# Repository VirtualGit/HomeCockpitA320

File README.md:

# A320 Home Cockpit
Home cockpit project of the Airbus A320 based on Arduino.

[Read more](https://github.com/VirtualGit/HomeCockpitA320/wiki/A320-Home-Cockpit)

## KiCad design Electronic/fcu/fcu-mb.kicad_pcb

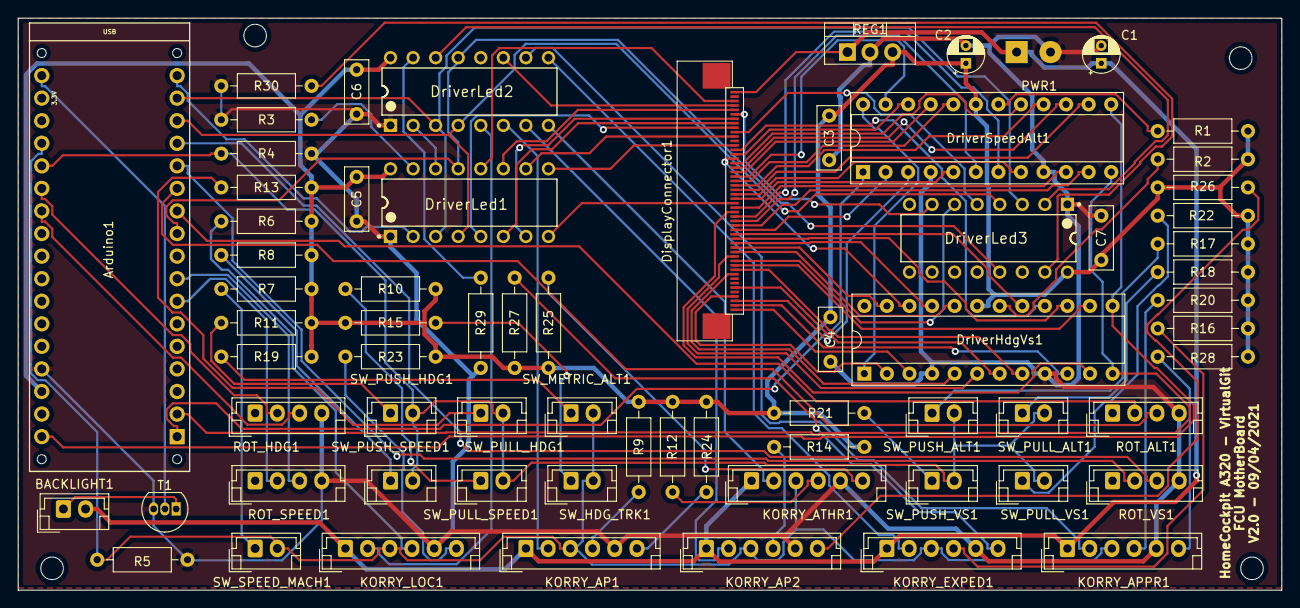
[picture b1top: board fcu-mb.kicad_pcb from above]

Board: 2 copper layers, 142.2 x 64.4 mm, 69 parts (0 on the bottom side), 103 nets.

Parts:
Arduino1: Arduino_Nano_v3.x; Arduino_Micro_Socket
BACKLIGHT1: Conn_01x02_Male; JST_EH_B2B-EH-A_1x02_P2.50mm_Vertical
C1: 100µF; CP_Radial_D4.0mm_P2.00mm
C2: 10µF; CP_Radial_D4.0mm_P2.00mm
C3, C4: 0,1µF; C_Disc_D7.0mm_W2.5mm_P5.00mm
C5, C6, C7: 1µF; C_Disc_D7.0mm_W2.5mm_P5.00mm
DisplayConnector1: Connector-FPC-50pins; Connector-FPC-50pins-0.5mm
DriverHdgVs1: MAX7219; DIP-24_W7.62mm_Socket
DriverLed1, DriverLed2, DriverLed3: TLC5917IN; Texas_Instruments-TLC5917IN-Manufacturer_Recommended
DriverSpeedAlt1: MAX7219; DIP-24_W7.62mm_Socket
KORRY_AP1, KORRY_AP2: Korry; JST_EH_B6B-EH-A_1x06_P2.50mm_Vertical
KORRY_APPR1: Korry; JST_EH_B6B-EH-A_1x06_P2.50mm_Vertical
KORRY_ATHR1: Korry; JST_EH_B6B-EH-A_1x06_P2.50mm_Vertical
KORRY_EXPED1: Korry; JST_EH_B6B-EH-A_1x06_P2.50mm_Vertical
KORRY_LOC1: Korry; JST_EH_B6B-EH-A_1x06_P2.50mm_Vertical
PWR1: Conn_Coaxial_Power; SolderWirePad_1x02_P3.81mm_Drill1mm
R1, R2: 9,53kohms; R_Axial_DIN0207_L6.3mm_D2.5mm_P10.16mm_Horizontal
R3, R29: 1kohms; R_Axial_DIN0207_L6.3mm_D2.5mm_P10.16mm_Horizontal
R4, R5: 100kOhms; R_Axial_DIN0207_L6.3mm_D2.5mm_P10.16mm_Horizontal
R6, R13: 33kOhms; R_Axial_DIN0207_L6.3mm_D2.5mm_P10.16mm_Horizontal
R7, R8: 8,2kOhms; R_Axial_DIN0207_L6.3mm_D2.5mm_P10.16mm_Horizontal
R9, R22: 120kOhms; R_Axial_DIN0207_L6.3mm_D2.5mm_P10.16mm_Horizontal
R10, R15: 15kOhms; R_Axial_DIN0207_L6.3mm_D2.5mm_P10.16mm_Horizontal
R11, R19: 22kOhms; R_Axial_DIN0207_L6.3mm_D2.5mm_P10.16mm_Horizontal
R12, R17: 47kOhms; R_Axial_DIN0207_L6.3mm_D2.5mm_P10.16mm_Horizontal
R14: 150kOhms; R_Axial_DIN0207_L6.3mm_D2.5mm_P10.16mm_Horizontal
R16, R18: 68kOhms; R_Axial_DIN0207_L6.3mm_D2.5mm_P10.16mm_Horizontal
R20, R21: 91kOhms; R_Axial_DIN0207_L6.3mm_D2.5mm_P10.16mm_Horizontal
R23, R24, R25, R26, R27, R28: 100Ohms; R_Axial_DIN0207_L6.3mm_D2.5mm_P10.16mm_Horizontal
R30: 2kohms; R_Axial_DIN0207_L6.3mm_D2.5mm_P10.16mm_Horizontal
REG1: L7805; TO-220-3_Vertical
ROT_ALT1: Rotary_Encoder; JST_EH_B4B-EH-A_1x04_P2.50mm_Vertical_RotaryEncoder
ROT_HDG1: Rotary_Encoder; JST_EH_B4B-EH-A_1x04_P2.50mm_Vertical_RotaryEncoder
ROT_SPEED1: Rotary_Encoder; JST_EH_B4B-EH-A_1x04_P2.50mm_Vertical_RotaryEncoder
ROT_VS1: Rotary_Encoder; JST_EH_B4B-EH-A_1x04_P2.50mm_Vertical_RotaryEncoder
SW_HDG_TRK1: SW_Push; JST_EH_B2B-EH-A_1x02_P2.50mm_Vertical
SW_METRIC_ALT1: SW_Push; JST_EH_B2B-EH-A_1x02_P2.50mm_Vertical
SW_PULL_ALT1: SW_Push; JST_EH_B2B-EH-A_1x02_P2.50mm_Vertical
SW_PULL_HDG1: SW_Push; JST_EH_B2B-EH-A_1x02_P2.50mm_Vertical
SW_PULL_SPEED1: SW_Push; JST_EH_B2B-EH-A_1x02_P2.50mm_Vertical
SW_PULL_VS1: SW_Push; JST_EH_B2B-EH-A_1x02_P2.50mm_Vertical
SW_PUSH_ALT1: SW_Push; JST_EH_B2B-EH-A_1x02_P2.50mm_Vertical
SW_PUSH_HDG1: SW_Push; JST_EH_B2B-EH-A_1x02_P2.50mm_Vertical
SW_PUSH_SPEED1: SW_Push; JST_EH_B2B-EH-A_1x02_P2.50mm_Vertical
SW_PUSH_VS1: SW_Push; JST_EH_B2B-EH-A_1x02_P2.50mm_Vertical
SW_SPEED_MACH1: SW_Push; JST_EH_B2B-EH-A_1x02_P2.50mm_Vertical
T1: BS170; TO-92_Inline

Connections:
+5V: Arduino1.VIN, C2.1, C3.1, C4.1, C5.2, C6.2, C7.2, DriverHdgVs1.19, DriverLed1.16, DriverLed2.16, DriverLed3.16, DriverSpeedAlt1.19, R1.1, R2.1, R6.2, R7.2, R8.2, R9.2, R10.2, R11.2, R12.2, R13.2, R14.2, R15.2, R16.2, R17.2, R18.2, R19.2, R20.2, R21.2, R22.2, R23.2, R24.2, R25.2, R26.2, R27.2, R28.2, REG1.3
BTN_GRP_1: Arduino1.A0, KORRY_AP1.3, KORRY_AP2.3, KORRY_APPR1.3, KORRY_ATHR1.3, KORRY_EXPED1.3, KORRY_LOC1.3, R5.2, SW_HDG_TRK1.2, SW_METRIC_ALT1.2, SW_SPEED_MACH1.2
BTN_GRP_2: Arduino1.A1, R4.2, SW_PULL_ALT1.2, SW_PULL_HDG1.2, SW_PULL_SPEED1.2, SW_PULL_VS1.2, SW_PUSH_ALT1.2, SW_PUSH_HDG1.2, SW_PUSH_SPEED1.2, SW_PUSH_VS1.2
DriverDigitClock: Arduino1.SCK, DriverHdgVs1.13, DriverSpeedAlt1.13
DriverDigitData: Arduino1.MOSI, DriverSpeedAlt1.1
DriverDigitLoad: Arduino1.SS, DriverHdgVs1.12, DriverSpeedAlt1.12
DriverLedClock: Arduino1.D11, DriverLed1.3, DriverLed2.3, DriverLed3.3
DriverLedData: Arduino1.D12, DriverLed1.2
DriverLedLoad: Arduino1.D10, DriverLed1.4, DriverLed2.4, DriverLed3.4
GND: Arduino1.GND1, C1.2, C2.2, C3.2, C4.2, C5.1, C6.1, C7.1, DriverHdgVs1.4, DriverHdgVs1.9, DriverLed1.1, DriverLed2.1, DriverLed3.1, DriverSpeedAlt1.4, DriverSpeedAlt1.9, KORRY_AP1.5, KORRY_AP2.5, KORRY_APPR1.5, KORRY_ATHR1.5, KORRY_EXPED1.5, KORRY_LOC1.5, PWR1.2, R3.1, R4.1, R5.1, R29.1, R30.1, REG1.2, ROT_ALT1.C, ROT_HDG1.C, ROT_SPEED1.C, ROT_VS1.C, T1.3
LedKorryAP1: DriverLed2.6, KORRY_AP1.2
LedKorryAP2: DriverLed2.7, KORRY_AP2.2
LedKorryAPPR: DriverLed2.10, KORRY_APPR1.2
LedKorryATHR: DriverLed2.8, KORRY_ATHR1.2
LedKorryEXPED: DriverLed2.9, KORRY_EXPED1.2
LedKorryLoc: DriverLed2.5, KORRY_LOC1.2
LedManagedALT: DisplayConnector1.6, DriverLed3.7
LedManagedHDG: DisplayConnector1.39, DriverLed3.6
LedManagedSpeed: DisplayConnector1.10, DriverLed3.5
LedOutputEnable: Arduino1.D5, DriverLed1.13, DriverLed2.13, DriverLed3.13
LedPadFPA: DisplayConnector1.5, DriverLed1.11
LedPadHDG: DisplayConnector1.7, DriverLed1.7
LedPadLAT: DisplayConnector1.13, DriverLed1.9
LedPadMACH: DisplayConnector1.8, DriverLed1.6
LedPadSPD: DisplayConnector1.9, DriverLed1.5
LedPadStaticALT: DisplayConnector1.3, DriverLed1.12
LedPadStaticLines: DisplayConnector1.4, DriverLed2.11
LedPadTRK: DisplayConnector1.26, DriverLed1.8
LedPadVS: DisplayConnector1.11, DriverLed1.10
unnamed: Arduino1.D13, T1.2
unnamed: BACKLIGHT1.1, T1.1
unnamed: DriverHdgVs1.1, DriverSpeedAlt1.24
unnamed: DriverHdgVs1.18, R2.2
unnamed: DriverLed1.14, DriverLed2.2
unnamed: DriverLed1.15, R3.2
unnamed: DriverLed2.14, DriverLed3.2
unnamed: DriverLed2.15, R29.2
unnamed: DriverLed3.15, R30.2
unnamed: DriverSpeedAlt1.18, R1.2
unnamed: KORRY_AP1.4, R9.1
unnamed: KORRY_AP1.6, R24.1
unnamed: KORRY_AP2.4, R14.1
unnamed: KORRY_AP2.6, R26.1
unnamed: KORRY_APPR1.4, R20.1
unnamed: KORRY_APPR1.6, R28.1
unnamed: KORRY_ATHR1.4, R12.1
unnamed: KORRY_ATHR1.6, R25.1
unnamed: KORRY_EXPED1.4, R16.1
unnamed: KORRY_EXPED1.6, R27.1
unnamed: KORRY_LOC1.4, R6.1
unnamed: KORRY_LOC1.6, R23.1
unnamed: R7.1, SW_SPEED_MACH1.1
unnamed: R8.1, SW_PUSH_SPEED1.1
unnamed: R10.1, SW_PULL_SPEED1.1
unnamed: R11.1, SW_PUSH_HDG1.1
unnamed: R13.1, SW_PULL_HDG1.1
unnamed: R15.1, SW_HDG_TRK1.1
unnamed: R17.1, SW_PUSH_ALT1.1
unnamed: R18.1, SW_PULL_ALT1.1
unnamed: R19.1, SW_METRIC_ALT1.1
unnamed: R21.1, SW_PUSH_VS1.1
unnamed: R22.1, SW_PULL_VS1.1
ROT_ALT_A: Arduino1.D6, ROT_ALT1.A
ROT_ALT_B: Arduino1.D7, ROT_ALT1.B
ROT_HDG_A: Arduino1.A2, ROT_HDG1.A
ROT_HDG_B: Arduino1.A3, ROT_HDG1.B
ROT_SPEED_A: Arduino1.D2, ROT_SPEED1.A
ROT_SPEED_B: Arduino1.D3, ROT_SPEED1.B
ROT_VS_A: Arduino1.D8, ROT_VS1.A
ROT_VS_B: Arduino1.D9, ROT_VS1.B
Vcc12V: BACKLIGHT1.2, C1.1, DisplayConnector1.1, KORRY_AP1.1, KORRY_AP2.1, KORRY_APPR1.1, KORRY_ATHR1.1, KORRY_EXPED1.1, KORRY_LOC1.1, PWR1.1, REG1.1
hdgVsA: DisplayConnector1.40, DriverHdgVs1.14
hdgVsB: DisplayConnector1.14, DriverHdgVs1.16
hdgVsC: DisplayConnector1.37, DriverHdgVs1.20
hdgVsD: DisplayConnector1.36, DriverHdgVs1.23
hdgVsDP: DisplayConnector1.16, DriverHdgVs1.22
hdgVsDig0: DisplayConnector1.47, DriverHdgVs1.2
hdgVsDig1: DisplayConnector1.28, DriverHdgVs1.11
hdgVsDig2: DisplayConnector1.38, DriverHdgVs1.6
hdgVsDig3: DisplayConnector1.45, DriverHdgVs1.7
hdgVsDig4: DisplayConnector1.50, DriverHdgVs1.3
hdgVsDig5: DisplayConnector1.49, DriverHdgVs1.10
hdgVsDig6: DisplayConnector1.42, DriverHdgVs1.5
hdgVsDig7: DisplayConnector1.41, DriverHdgVs1.8
hdgVsE: DisplayConnector1.35, DriverHdgVs1.21
hdgVsF: DisplayConnector1.34, DriverHdgVs1.15
hdgVsG: DisplayConnector1.33, DriverHdgVs1.17
speedAltA: DisplayConnector1.23, DriverSpeedAlt1.14
speedAltB: DisplayConnector1.22, DriverSpeedAlt1.16
speedAltC: DisplayConnector1.21, DriverSpeedAlt1.20
speedAltD: DisplayConnector1.20, DriverSpeedAlt1.23
speedAltDP: DisplayConnector1.15, DriverSpeedAlt1.22
speedAltDig0: DisplayConnector1.32, DriverSpeedAlt1.2
speedAltDig1: DisplayConnector1.31, DriverSpeedAlt1.11
speedAltDig2: DisplayConnector1.30, DriverSpeedAlt1.6
speedAltDig3: DisplayConnector1.29, DriverSpeedAlt1.7
speedAltDig4: DisplayConnector1.48, DriverSpeedAlt1.3
speedAltDig5: DisplayConnector1.27, DriverSpeedAlt1.10
speedAltDig6: DisplayConnector1.25, DriverSpeedAlt1.5
speedAltDig7: DisplayConnector1.24, DriverSpeedAlt1.8
speedAltE: DisplayConnector1.19, DriverSpeedAlt1.21
speedAltF: DisplayConnector1.18, DriverSpeedAlt1.15
speedAltG: DisplayConnector1.17, DriverSpeedAlt1.17

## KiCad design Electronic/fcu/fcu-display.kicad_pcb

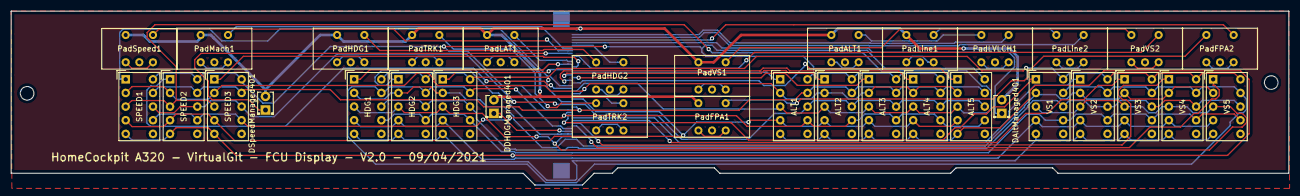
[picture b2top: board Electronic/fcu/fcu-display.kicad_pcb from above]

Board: 2 copper layers, 238.0 x 32.4 mm, 35 parts (1 on the bottom side), 66 nets.

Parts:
ALT1, ALT2, ALT3, ALT4, ALT5: HDSP-7401
DAltManaged401: LED; LED_D2.0mm_W4.0mm_H2.8mm_FlatTop
DDHDGManaged401: LED; LED_D2.0mm_W4.0mm_H2.8mm_FlatTop
DSpeedManaged401: LED; LED_D2.0mm_W4.0mm_H2.8mm_FlatTop
DisplayConnector1: Connector-FPC-50pins; Connector-FPC-50pins-0.5mm
HDG1, HDG2, HDG3: HDSP-7401
PadALT1: LedPad; PadLed-KingBright-DE-2YD
PadFPA1, PadFPA2: LedPad; PadLed-KingBright-DE-2YD
PadHDG1, PadHDG2: LedPad; PadLed-KingBright-DE-2YD
PadLAT1: LedPad; PadLed-KingBright-DE-2YD
PadLVLCH1: LedPad; PadLed-KingBright-DE-2YD
PadLine1, PadLine2: LedPad; PadLed-KingBright-DE-2YD
PadMach1: LedPad; PadLed-KingBright-DE-2YD
PadSpeed1: LedPad; PadLed-KingBright-DE-2YD
PadTRK1, PadTRK2: LedPad; PadLed-KingBright-DE-2YD
PadVS1, PadVS2: LedPad; PadLed-KingBright-DE-2YD
SPEED1, SPEED2, SPEED3: HDSP-7401
VS1, VS2, VS3, VS4, VS5: HDSP-7401

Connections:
LedManagedALT: DAltManaged401.1, DisplayConnector1.45
LedManagedHDG: DDHDGManaged401.1, DisplayConnector1.12
LedManagedSpeed: DSpeedManaged401.1, DisplayConnector1.41
LedPadFPA: DisplayConnector1.46, PadFPA2.1
LedPadHDG: DisplayConnector1.44, PadHDG2.1
LedPadLAT: DisplayConnector1.38, PadLAT1.1
LedPadMACH: DisplayConnector1.43, PadMach1.1
LedPadSPD: DisplayConnector1.42, PadSpeed1.1
LedPadStaticALT: DisplayConnector1.48, PadLVLCH1.1
LedPadStaticLines: DisplayConnector1.47, PadLine2.1
LedPadTRK: DisplayConnector1.25, PadTRK2.1
LedPadVS: DisplayConnector1.40, PadVS2.1
unnamed: PadALT1.1, PadLVLCH1.3
unnamed: PadALT1.4, PadALT1.6
unnamed: PadFPA1.1, PadFPA2.3
unnamed: PadFPA1.4, PadFPA1.6
unnamed: PadFPA2.4, PadFPA2.6
unnamed: PadHDG1.1, PadHDG2.3
unnamed: PadHDG1.4, PadHDG1.6
unnamed: PadHDG2.4, PadHDG2.6
unnamed: PadLAT1.4, PadLAT1.6
unnamed: PadLVLCH1.4, PadLVLCH1.6
unnamed: PadLine1.1, PadLine2.3
unnamed: PadLine1.4, PadLine1.6
unnamed: PadLine2.4, PadLine2.6
unnamed: PadMach1.4, PadMach1.6
unnamed: PadSpeed1.4, PadSpeed1.6
unnamed: PadTRK1.1, PadTRK2.3
unnamed: PadTRK1.4, PadTRK1.6
unnamed: PadTRK2.4, PadTRK2.6
unnamed: PadVS1.1, PadVS2.3
unnamed: PadVS1.4, PadVS1.6
unnamed: PadVS2.4, PadVS2.6
Vcc12V: DAltManaged401.2, DDHDGManaged401.2, DSpeedManaged401.2, DisplayConnector1.50, PadALT1.3, PadFPA1.3, PadHDG1.3, PadLAT1.3, PadLine1.3, PadMach1.3, PadSpeed1.3, PadTRK1.3, PadVS1.3
hdgVsA: DisplayConnector1.11, HDG2.1
hdgVsB: DisplayConnector1.37, HDG1.1
hdgVsC: DisplayConnector1.14, VS5.1
hdgVsD: DisplayConnector1.15, VS4.1
hdgVsDP: DisplayConnector1.35, HDG3.1
hdgVsDig0: DisplayConnector1.4, HDG1.7, HDG2.7, HDG3.7, VS1.7, VS2.7, VS3.7, VS4.7, VS5.7
hdgVsDig1: DisplayConnector1.23, HDG1.10, HDG2.10, HDG3.10, VS1.10, VS2.10, VS3.10, VS4.10, VS5.10
hdgVsDig2: DisplayConnector1.13, HDG1.9, HDG2.9, HDG3.9, VS1.9, VS2.9, VS3.9, VS4.9, VS5.9
hdgVsDig3: DisplayConnector1.6, HDG1.8, HDG2.8, HDG3.8, VS1.8, VS2.8, VS3.8, VS4.8, VS5.8
hdgVsDig4: DisplayConnector1.1, HDG1.5, HDG2.5, HDG3.5, VS1.5, VS2.5, VS3.5, VS4.5, VS5.5
hdgVsDig5: DisplayConnector1.2, HDG1.4, HDG2.4, HDG3.4, VS1.4, VS2.4, VS3.4, VS4.4, VS5.4
hdgVsDig6: DisplayConnector1.9, HDG1.2, HDG2.2, HDG3.2, VS1.2, VS2.2, VS3.2, VS4.2, VS5.2
hdgVsDig7: DisplayConnector1.10, HDG1.3, HDG2.3, HDG3.3, VS1.3, VS2.3, VS3.3, VS4.3, VS5.3
hdgVsE: DisplayConnector1.16, VS3.1
hdgVsF: DisplayConnector1.17, VS2.1
hdgVsG: DisplayConnector1.18, VS1.1
speedAltA: DisplayConnector1.28, SPEED2.1
speedAltB: DisplayConnector1.29, SPEED1.1
speedAltC: ALT5.1, DisplayConnector1.30
speedAltD: ALT4.1, DisplayConnector1.31
speedAltDP: DisplayConnector1.36, SPEED3.1
speedAltDig0: ALT1.7, ALT2.7, ALT3.7, ALT4.7, ALT5.7, DisplayConnector1.19, SPEED1.7, SPEED2.7, SPEED3.7
speedAltDig1: ALT1.10, ALT2.10, ALT3.10, ALT4.10, ALT5.10, DisplayConnector1.20, SPEED1.10, SPEED2.10, SPEED3.10
speedAltDig2: ALT1.9, ALT2.9, ALT3.9, ALT4.9, ALT5.9, DisplayConnector1.21, SPEED1.9, SPEED2.9, SPEED3.9
speedAltDig3: ALT1.8, ALT2.8, ALT3.8, ALT4.8, ALT5.8, DisplayConnector1.22, SPEED1.8, SPEED2.8, SPEED3.8
speedAltDig4: ALT1.5, ALT2.5, ALT3.5, ALT4.5, ALT5.5, DisplayConnector1.3, SPEED1.5, SPEED2.5, SPEED3.5
speedAltDig5: ALT1.4, ALT2.4, ALT3.4, ALT4.4, ALT5.4, DisplayConnector1.24, SPEED1.4, SPEED2.4, SPEED3.4
speedAltDig6: ALT1.2, ALT2.2, ALT3.2, ALT4.2, ALT5.2, DisplayConnector1.26, SPEED1.2, SPEED2.2, SPEED3.2
speedAltDig7: ALT1.3, ALT2.3, ALT3.3, ALT4.3, ALT5.3, DisplayConnector1.27, SPEED1.3, SPEED2.3, SPEED3.3
speedAltE: ALT3.1, DisplayConnector1.32
speedAltF: ALT2.1, DisplayConnector1.33
speedAltG: ALT1.1, DisplayConnector1.34

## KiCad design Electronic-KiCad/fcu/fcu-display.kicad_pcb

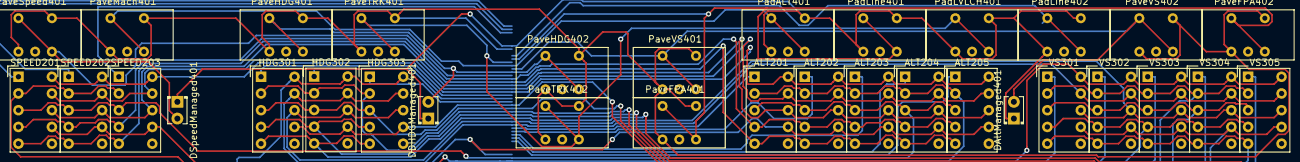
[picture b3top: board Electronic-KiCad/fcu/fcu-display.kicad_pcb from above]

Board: 2 copper layers, 34 parts (1 on the bottom side), 41 nets.

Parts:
ALT201, ALT202, ALT203, ALT204, ALT205: HDSP-7403; HDSP-7401
DAltManaged401: LED; LED_D2.0mm_W4.0mm_H2.8mm_FlatTop
DDHDGManaged401: LED; LED_D2.0mm_W4.0mm_H2.8mm_FlatTop
DSpeedManaged401: LED; LED_D2.0mm_W4.0mm_H2.8mm_FlatTop
HDG301, HDG302, HDG303: HDSP-7403; HDSP-7401
PadALT401: LedPave-home-cockpit-library; PadLed-KingBright-DE-2YD
PadLVLCH401: LedPave-home-cockpit-library; PadLed-KingBright-DE-2YD
PadLine401, PadLine402: LedPave-home-cockpit-library; PadLed-KingBright-DE-2YD
PaveFPA401, PaveFPA402: LedPave-home-cockpit-library; PadLed-KingBright-DE-2YD
PaveHDG401, PaveHDG402: LedPave-home-cockpit-library; PadLed-KingBright-DE-2YD
PaveMach401: LedPave-home-cockpit-library; PadLed-KingBright-DE-2YD
PaveSpeed401: LedPave-home-cockpit-library; PadLed-KingBright-DE-2YD
PaveTRK401, PaveTRK402: LedPave-home-cockpit-library; PadLed-KingBright-DE-2YD
PaveVS401, PaveVS402: LedPave-home-cockpit-library; PadLed-KingBright-DE-2YD
SPEED201, SPEED202, SPEED203: HDSP-7403; HDSP-7401
U101: Connector-FPC-50pins; Connector-FPC-50pins-0.5mm
VS301, VS302, VS303, VS304, VS305: HDSP-7403; HDSP-7401

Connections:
Dr3Dig0: PaveFPA401.1, PaveFPA401.4, PaveFPA402.1, PaveFPA402.4, PaveHDG401.1, PaveHDG401.4, PaveHDG402.1, PaveHDG402.4, PaveMach401.1, PaveMach401.4, PaveSpeed401.1, PaveSpeed401.4, PaveTRK401.1, PaveTRK401.4, PaveTRK402.1, PaveTRK402.4, PaveVS401.1, PaveVS401.4, PaveVS402.1, PaveVS402.4, U101.41
Dr3Dig1: DAltManaged401.1, DDHDGManaged401.1, DSpeedManaged401.1, PadALT401.1, PadALT401.4, PadLVLCH401.1, PadLVLCH401.4, PadLine401.1, PadLine401.4, PadLine402.1, PadLine402.4, U101.42
Dr3SegA: DSpeedManaged401.2, PaveSpeed401.3, PaveSpeed401.6, U101.33
Dr3SegB: DDHDGManaged401.2, PaveHDG401.3, PaveHDG401.6, PaveHDG402.3, PaveHDG402.6, U101.34
Dr3SegC: DAltManaged401.2, PaveVS401.3, PaveVS401.6, PaveVS402.3, PaveVS402.6, U101.35
Dr3SegD: PadALT401.3, PadALT401.6, PaveMach401.3, PaveMach401.6, U101.36
Dr3SegE: PadLVLCH401.3, PadLVLCH401.6, PaveTRK401.3, PaveTRK401.6, PaveTRK402.3, PaveTRK402.6, U101.37
Dr3SegF: PadLine401.3, PadLine401.6, PaveFPA401.3, PaveFPA401.6, PaveFPA402.3, PaveFPA402.6, U101.38
Dr3SegG: PadLine402.3, PadLine402.6, U101.39
hdgVsA: HDG301.10, HDG302.10, HDG303.10, U101.6, VS301.10, VS302.10, VS303.10, VS304.10, VS305.10
hdgVsB: HDG301.9, HDG302.9, HDG303.9, U101.18, VS301.9, VS302.9, VS303.9, VS304.9, VS305.9
hdgVsC: HDG301.8, HDG302.8, HDG303.8, U101.19, VS301.8, VS302.8, VS303.8, VS304.8, VS305.8
hdgVsD: HDG301.5, HDG302.5, HDG303.5, U101.20, VS301.5, VS302.5, VS303.5, VS304.5, VS305.5
hdgVsDP: HDG301.7, HDG302.7, HDG303.7, U101.24, VS301.7, VS302.7, VS303.7, VS304.7, VS305.7
hdgVsDig0: HDG303.1, U101.25
hdgVsDig1: HDG302.1, U101.26
hdgVsDig2: HDG301.1, U101.27
hdgVsDig3: U101.1, VS305.1
hdgVsDig4: U101.2, VS304.1
hdgVsDig5: U101.3, VS303.1
hdgVsDig6: U101.4, VS302.1
hdgVsDig7: U101.5, VS301.1
hdgVsE: HDG301.4, HDG302.4, HDG303.4, U101.21, VS301.4, VS302.4, VS303.4, VS304.4, VS305.4
hdgVsF: HDG301.2, HDG302.2, HDG303.2, U101.22, VS301.2, VS302.2, VS303.2, VS304.2, VS305.2
hdgVsG: HDG301.3, HDG302.3, HDG303.3, U101.23, VS301.3, VS302.3, VS303.3, VS304.3, VS305.3
speedAltA: ALT201.10, ALT202.10, ALT203.10, ALT204.10, ALT205.10, SPEED201.10, SPEED202.10, SPEED203.10, U101.28
speedAltB: ALT201.9, ALT202.9, ALT203.9, ALT204.9, ALT205.9, SPEED201.9, SPEED202.9, SPEED203.9, U101.29
speedAltC: ALT201.8, ALT202.8, ALT203.8, ALT204.8, ALT205.8, SPEED201.8, SPEED202.8, SPEED203.8, U101.30
speedAltD: ALT201.5, ALT202.5, ALT203.5, ALT204.5, ALT205.5, SPEED201.5, SPEED202.5, SPEED203.5, U101.31
speedAltDP: ALT201.7, ALT202.7, ALT203.7, ALT204.7, ALT205.7, SPEED201.7, SPEED202.7, SPEED203.7, U101.9
speedAltDig0: SPEED203.1, U101.46
speedAltDig1: SPEED202.1, U101.47
speedAltDig2: SPEED201.1, U101.48
speedAltDig3: ALT205.1, U101.13
speedAltDig4: ALT204.1, U101.14
speedAltDig5: ALT203.1, U101.15
speedAltDig6: ALT202.1, U101.16
speedAltDig7: ALT201.1, U101.17
speedAltE: ALT201.4, ALT202.4, ALT203.4, ALT204.4, ALT205.4, SPEED201.4, SPEED202.4, SPEED203.4, U101.32
speedAltF: ALT201.2, ALT202.2, ALT203.2, ALT204.2, ALT205.2, SPEED201.2, SPEED202.2, SPEED203.2, U101.7
speedAltG: ALT201.3, ALT202.3, ALT203.3, ALT204.3, ALT205.3, SPEED201.3, SPEED202.3, SPEED203.3, U101.8

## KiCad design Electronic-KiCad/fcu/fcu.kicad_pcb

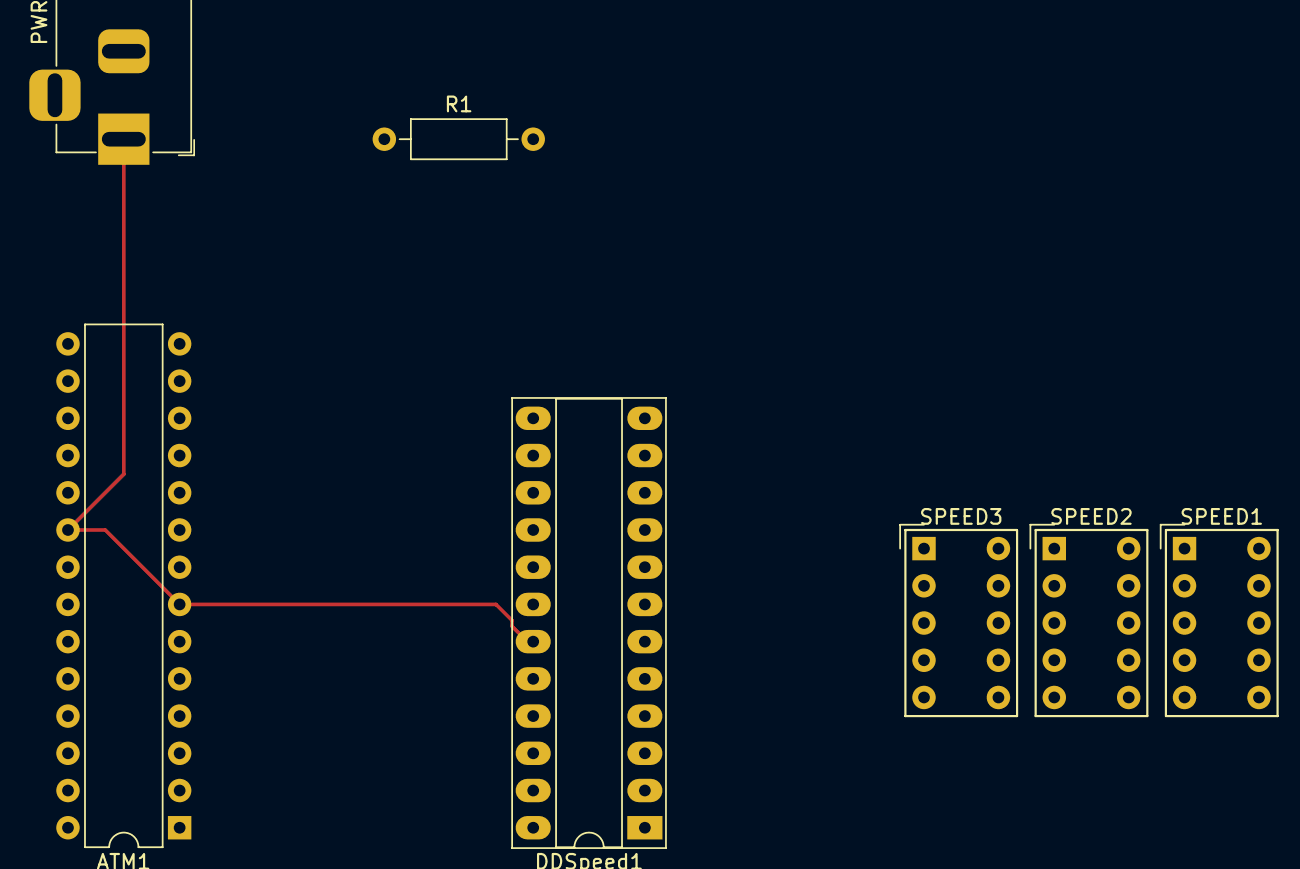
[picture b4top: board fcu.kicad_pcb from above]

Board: 2 copper layers, 7 parts (0 on the bottom side), 17 nets.

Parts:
ATM1: ATmega328P-PU; DIP-28_W7.62mm
DDSpeed1: MAX7219; DIP-24_W7.62mm_Socket_LongPads
PWR1: Conn_Coaxial_Power; BarrelJack_Horizontal
R1: 9,53ohms; R_Axial_DIN0207_L6.3mm_D2.5mm_P10.16mm_Horizontal
SPEED1, SPEED2, SPEED3: HDSP-7403; HDSP-7401

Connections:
/speedA: DDSpeed1.14, SPEED1.10, SPEED2.10, SPEED3.10
/speedB: DDSpeed1.16, SPEED1.9, SPEED2.9, SPEED3.9
/speedC: DDSpeed1.20, SPEED1.8, SPEED2.8, SPEED3.8
/speedD: DDSpeed1.23, SPEED1.5, SPEED2.5, SPEED3.5
/speedDP: DDSpeed1.22, SPEED1.7, SPEED2.7, SPEED3.7
/speedE: DDSpeed1.21, SPEED1.4, SPEED2.4, SPEED3.4
/speedF: DDSpeed1.15, SPEED1.2, SPEED2.2, SPEED3.2
/speedG: DDSpeed1.17, SPEED1.3, SPEED2.3, SPEED3.3
GND: ATM1.8, ATM1.22, DDSpeed1.4, DDSpeed1.9, PWR1.2
unnamed: ATM1.10, DDSpeed1.12
unnamed: ATM1.11, DDSpeed1.13
unnamed: ATM1.12, DDSpeed1.1
unnamed: ATM1.7, ATM1.20, DDSpeed1.19, PWR1.1, R1.1
unnamed: DDSpeed1.2, SPEED3.1, SPEED3.6
unnamed: DDSpeed1.6, SPEED1.1, SPEED1.6
unnamed: DDSpeed1.11, SPEED2.1, SPEED2.6
unnamed: DDSpeed1.18, R1.2

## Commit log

2020-01-19 Add Electronic folder and first EAGLE lib MAX7219
2020-02-03 Add Eagle libraries for FCU
2020-02-03 Add datasheets for FCU parts
2020-02-03 Add FCU schema and board, display part.
2021-02-13 First FCU draft with KiCad
2021-02-16 First draft complete for FCU MB (MotherBoard) and FCU Display.
2021-02-16 Remove old electronic files (Eagle)
2021-02-16 Add missing files
2021-02-16 Rename Electronic directory
2021-02-17 Add freerouting tool (from https://github.com/freerouting/freerouting)
2021-02-17 Remove draft schema
2021-02-17 Remove undesired, generated files
2021-02-17 Update gitignore file
2021-02-17 Update fcu schemas and libraries
2021-02-17 Update references to symbol in right library
2021-02-17 Update gitignore
2021-02-17 Remove undesired file
2021-02-17 Update FCU display board with routing
2021-02-17 Adust fcu display pcb layout Add Vcc to rotary encoder and update pcb with jst +1 pin
2021-02-20 Add first arduino libraries and test fcu file
2021-02-20 Add JHBridge software first draft version
2021-02-20 [JHBridge] Add tab for generating files
2021-02-21 Update JHBridge and JHArduino library to remove variable names
    Update JHBridge and JHArduino library to remove variable names and use
    an enum instead. All JeeHell parameters are in parameters.json. This
    file is the reference, from it, the parameters.h of JHArudino is
    generated. parameter.json is also used by JHBridge to generate JeeHell
    FMGSserver.iocp.ini file for a given board configuration (boards must be
    connected at the generation time to know which parameter are used and
2021-02-21 Add Analog_Buttons to the libraries
2021-02-21 Update SerialPort reading, because in case of quick new lines, readLine may stop in the middle of one line
2021-02-21 Update JHArduino library to send new values (buttons, then rotary encoders)
2021-02-21 Update fcu arduino test to add a button
2021-02-21 Add rotary encoder library
2021-02-21 Update parameter.json to add a rotary parameter
2021-02-21 Add a rotary encoder to the fcu test arduino project
2021-02-21 Add Arduino micro symbol and footprint
2021-02-21 Normalize parameters.json
2021-02-23 Update FCU PCB net routing
2021-02-25 Finalise first FCU PCB version
2021-02-25 Ignore gerber files
2021-04-02 switch types from int to long
2021-04-02 Update parameters.h file of JHArduino lib
2021-04-02 Update LedControl lib for improving common anode behavior.
2021-04-02 Update fcu arduino soft : digits and rotary encoders are ok
2021-04-07 Add information on identification log
2021-04-07 Change variable size type to size_t
2021-04-07 Change JHBridge default tab
2021-04-07 Update parameters.json file with new consolidated informations
2021-04-07 Change the way JHBridge handle SIOCVariable to allow correct export to both Arduino library and FMGS config file
2021-04-11 Update electornic schema of FCU MotherBoard and Display. Replace MAX7219 for leds to dedicated TLC5917.
2021-04-11 Adjust resistor values for TLC5917
2021-04-11 PCB changed after gerber export
2021-04-11 Add FCU PCB images
